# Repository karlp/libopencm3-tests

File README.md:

# Cross target tests for libopencm3

libopencm3(http://github.com/libopencm3/libopencm3) pull requests are often
hard to review.  It can be hard to see the impact on "user" land code, it can
be hard to see how the behaviour changes from a->b.

This repository contains testing frameworks I've put together to help with
cross target testing, with the aim of making them as automated as possible.

General plan is something like....

1. make -C libopencm3 clean all -j8
2. make -C tests/xxx clean all flash test V=1
3. cd libopencm3
4. git checkout proposed-new-code
5. return to step 1

Mileage _will_ vary.

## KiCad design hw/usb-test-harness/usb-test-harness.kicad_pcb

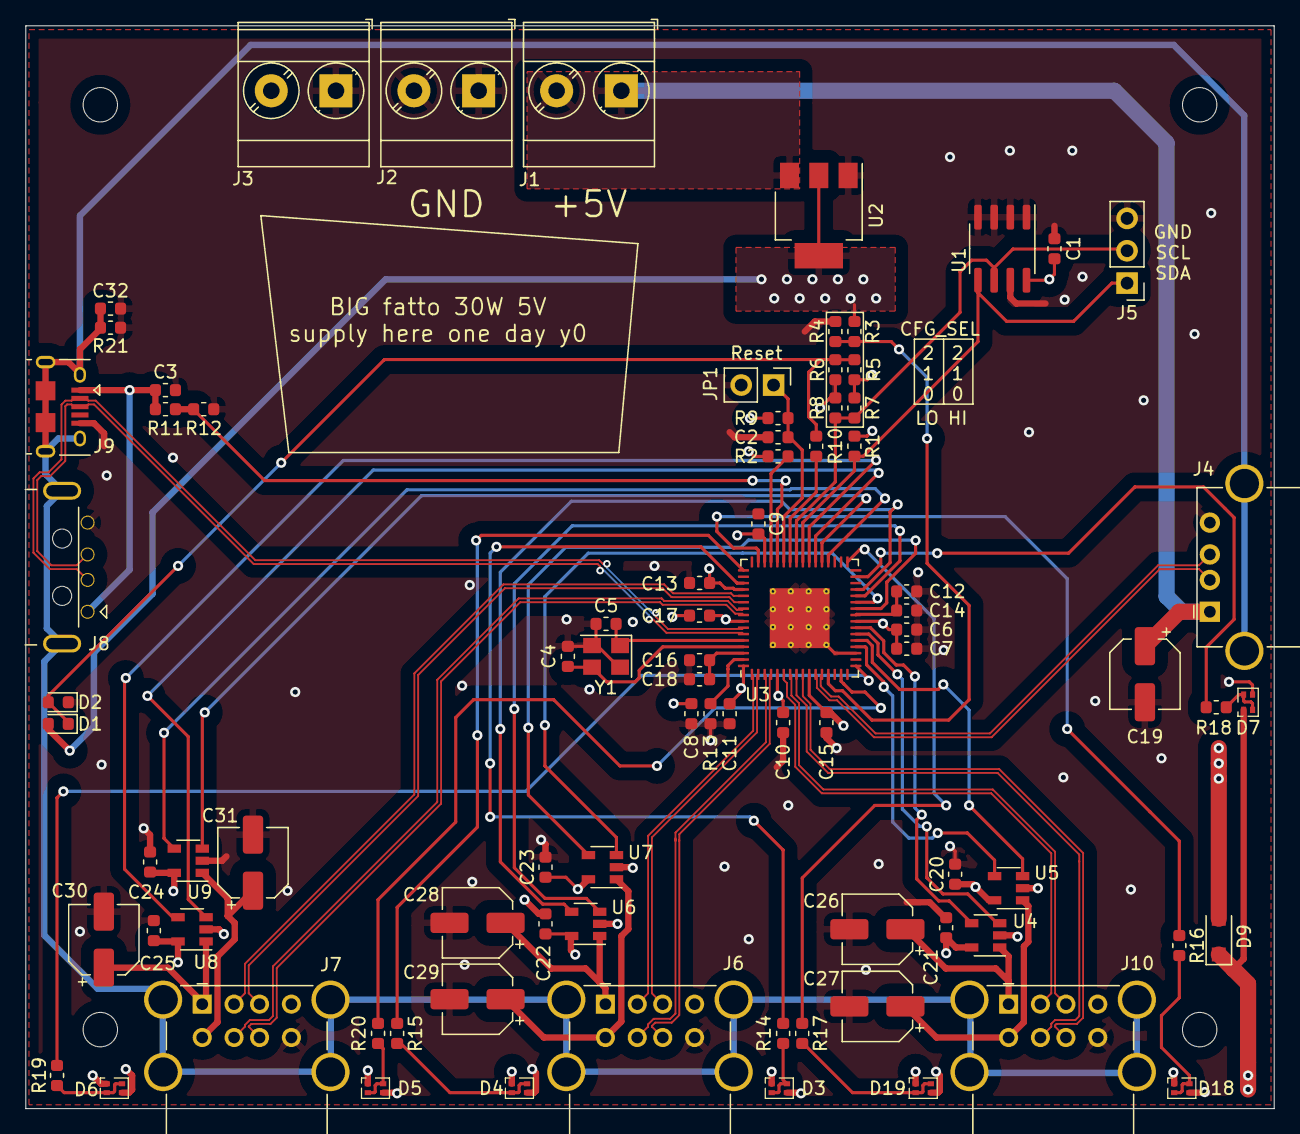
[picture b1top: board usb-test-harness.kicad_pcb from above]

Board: 4 copper layers, 98.0 x 85.0 mm, 88 parts (0 on the bottom side), 67 nets.

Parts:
C1, C2, C7, C9, C10, C11, C13, C14, C15, C17, C18, C32: .1uF; C_0603_1608Metric
C3: 2.2uF; C_0603_1608Metric
C4, C5: 33pF; C_0603_1608Metric
C6, C8, C12, C16, C20, C21, C22, C23, C24, C25: 1uF; C_0603_1608Metric
C19, C26, C27, C28, C29, C30, C31: 100uF; CP_Elec_5x5.4
D1: HS1B; LED_0603_1608Metric
D2: HS1A; LED_0603_1608Metric
D3, D4, D5, D6, D7, D18, D19: LTST-C295KGKRKT; LED_LiteOn_LTST-C295K
D9: D_Small; D_SOD-123F
H1, H2, H3, H4: MountingHole; MountingHole_2.7mm_M2.5
J1: 5V_RAW; TerminalBlock_Phoenix_MKDS-3-2-5.08_1x02_P5.08mm_Horizontal
J2: GND; TerminalBlock_Phoenix_MKDS-3-2-5.08_1x02_P5.08mm_Horizontal
J3: V_EXT; TerminalBlock_Phoenix_MKDS-3-2-5.08_1x02_P5.08mm_Horizontal
J4: USB_A (female down); USB_A_Stewart_SS-52100-001_Horizontal
J5: Conn_01x03_Male; PinHeader_1x03_P2.54mm_Vertical
J6, J7, J10: USB_A_DUAL; USB_A_Wuerth_61400826021_Horizontal_Stacked
J8: USB_A SOFNG USB-05; USB_A_Plug_SOFNG_USB-05
J9: USB_B_Micro (up); USB_Micro-B_Amphenol_10118194-0001LF_Horizontal
JP1: Jumper_NO_Small; PinHeader_1x02_P2.54mm_Vertical
R1, R2, R3, R4, R5, R6, R7, R8: 10k; R_0603_1608Metric
R9, R11, R12: 100k; R_0603_1608Metric
R10, R14, R15, R16, R17, R18, R19, R20, R21: 330; R_0603_1608Metric
R13: 12k; R_0603_1608Metric
U1: FT24C02A; SOIC-8_3.9x4.9mm_P1.27mm
U2: SE5120ST33; SOT-223-3_TabPin2
U3: USB2517; QFN-64-1EP_9x9mm_P0.5mm_EP4.7x4.7mm_ThermalVias
U4, U5, U6, U7, U8, U9: APL3511C; SOT-23-5
Y1: 24MHz; Crystal_SMD_3225-4Pin_3.2x2.5mm

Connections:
+3V3: C1.1, C6.1, C7.1, C8.1, C9.1, C10.1, C11.1, C13.1, C15.1, C17.1, D1.2, D9.2, R1.1, R2.1, R3.1, R5.1, R7.1, R9.1, U1.8, U2.2, U3.5, U3.10, U3.24, U3.46, U3.52, U3.57, U3.64
+5V: C19.1, C20.1, C21.1, C22.1, C23.1, C24.1, C25.1, J1.1, J1.2, J4.1, U2.3, U4.5, U5.5, U6.5, U7.5, U8.5, U9.5
/downstream-port-power/DS+: J4.3, U3.12
/downstream-port-power/DS-: J4.2, U3.11
/downstream-port-power/EN1: U3.23, U4.4
/downstream-port-power/EN2: U3.20, U5.4
/downstream-port-power/EN3: U3.29, U6.4
/downstream-port-power/EN4: U3.26, U7.4
/downstream-port-power/EN5: U3.39, U8.4
/downstream-port-power/EN6: U3.36, U9.4
/downstream-port-power/OC1: U3.22, U4.3
/downstream-port-power/OC2: U3.21, U5.3
/downstream-port-power/OC3: U3.28, U6.3
/downstream-port-power/OC4: U3.27, U7.3
/downstream-port-power/OC5: U3.38, U8.3
/downstream-port-power/OC6: U3.37, U9.3
/downstream-port-power/U1+: J10.3, U3.7
/downstream-port-power/U1-: J10.2, U3.6
/downstream-port-power/U2+: J10.7, U3.9
/downstream-port-power/U2-: J10.6, U3.8
/downstream-port-power/U3+: J6.3, U3.2
/downstream-port-power/U3-: J6.2, U3.1
/downstream-port-power/U4+: J6.7, U3.4
/downstream-port-power/U4-: J6.6, U3.3
/downstream-port-power/U5+: J7.3, U3.54
/downstream-port-power/U5-: J7.2, U3.53
/downstream-port-power/U6+: J7.7, U3.56
/downstream-port-power/U6-: J7.6, U3.55
/downstream-port-power/VBUS1: C26.1, J10.1, U4.1
/downstream-port-power/VBUS2: C27.1, J10.5, U5.1
/downstream-port-power/VBUS3: C28.1, J6.1, U6.1
/downstream-port-power/VBUS4: C29.1, J6.5, U7.1
/downstream-port-power/VBUS5: C30.1, J7.1, U8.1
/downstream-port-power/VBUS6: C31.1, J7.5, U9.1
/upstream-config-leds/CFG_SEL0: J5.2, R7.2, R8.1, U1.6, U3.41
/upstream-config-leds/CFG_SEL1: D1.1, D2.2, R5.2, R6.1, R10.1
/upstream-config-leds/CFG_SEL1_A: R10.2, U3.42
/upstream-config-leds/CFG_SEL2: R3.2, R4.1, U3.13
/upstream-config-leds/EE_SDA: J5.1, R1.2, U1.5, U3.40
/upstream-config-leds/LA_1-3: D3.2, D3.3, R14.2
/upstream-config-leds/LA_2-4: D4.2, D4.3, R15.2
/upstream-config-leds/LA_3-1: D18.2, D18.3, R16.2
/upstream-config-leds/LA_4-2: D19.2, D19.3, R17.2
/upstream-config-leds/LA_5-DS: D7.2, D7.3, R18.2
/upstream-config-leds/LA_6-6: D6.2, D6.3, R19.2
/upstream-config-leds/LA_7-5: D5.2, D5.3, R20.2
/upstream-config-leds/LED_A1: R14.1, U3.51
/upstream-config-leds/LED_A2: R15.1, U3.49
/upstream-config-leds/LED_A3: R16.1, U3.47
/upstream-config-leds/LED_A4: R17.1, U3.33
/upstream-config-leds/LED_A5: R18.1, U3.31
/upstream-config-leds/LED_A6: R19.1, U3.17
/upstream-config-leds/LED_A7: R20.1, U3.15
/upstream-config-leds/LED_DRIVE: D3.1, D4.1, D5.1, D6.1, D7.1, D9.1, D18.1, D19.1
/upstream-config-leds/LOCAL_PWR: R2.2, U3.45
/upstream-config-leds/RBIAS: R13.1, U3.63
/upstream-config-leds/UP+: J8.3, J9.3, U3.59
/upstream-config-leds/UP-: J8.2, J9.2, U3.58
/upstream-config-leds/VBUS_DET: R11.2, R12.1, U3.44
/upstream-config-leds/VBUS_UP: C3.1, J8.1, J9.1, R11.1
/upstream-config-leds/VDD18: C12.1, C14.1, U3.25
/upstream-config-leds/VDD18PLL: C16.1, C18.1, U3.62
/upstream-config-leds/XTAL1: C4.2, U3.61, Y1.3
/upstream-config-leds/XTAL2: C5.2, U3.60, Y1.1
/upstream-config-leds/~RESET: C2.1, JP1.1, R9.2, U3.43
GND: C1.2, C2.2, C3.2, C4.1, C5.1, C6.2, C7.2, C8.2, C9.2, C10.2, C11.2, C12.2, C13.2, C14.2, C15.2, C16.2, C17.2, C18.2, C19.2, C20.2, C21.2, C22.2, C23.2, C24.2, C25.2, C26.2, C27.2, C28.2, C29.2, C30.2, C31.2, C32.1, D2.1, D3.4, D4.4, D5.4, D6.4, D7.4, D18.4, D19.4, J2.1, J2.2, J3.1, J4.4, J5.3, J6.4, J6.8, J7.4, J7.8, J8.4, J9.5, J10.4, J10.8, JP1.2, R4.2, R6.2, R8.2, R12.2, R13.2, R21.1, U1.1, U1.2, U1.3, U1.4, U1.7, U2.1, U3.19, U3.65, U4.2, U5.2, U6.2, U7.2, U8.2, U9.2, Y1.2, Y1.4
GNDPWR: C32.2, J4.5, J6.9, J7.9, J8.5, J9.6, J10.9, R21.2

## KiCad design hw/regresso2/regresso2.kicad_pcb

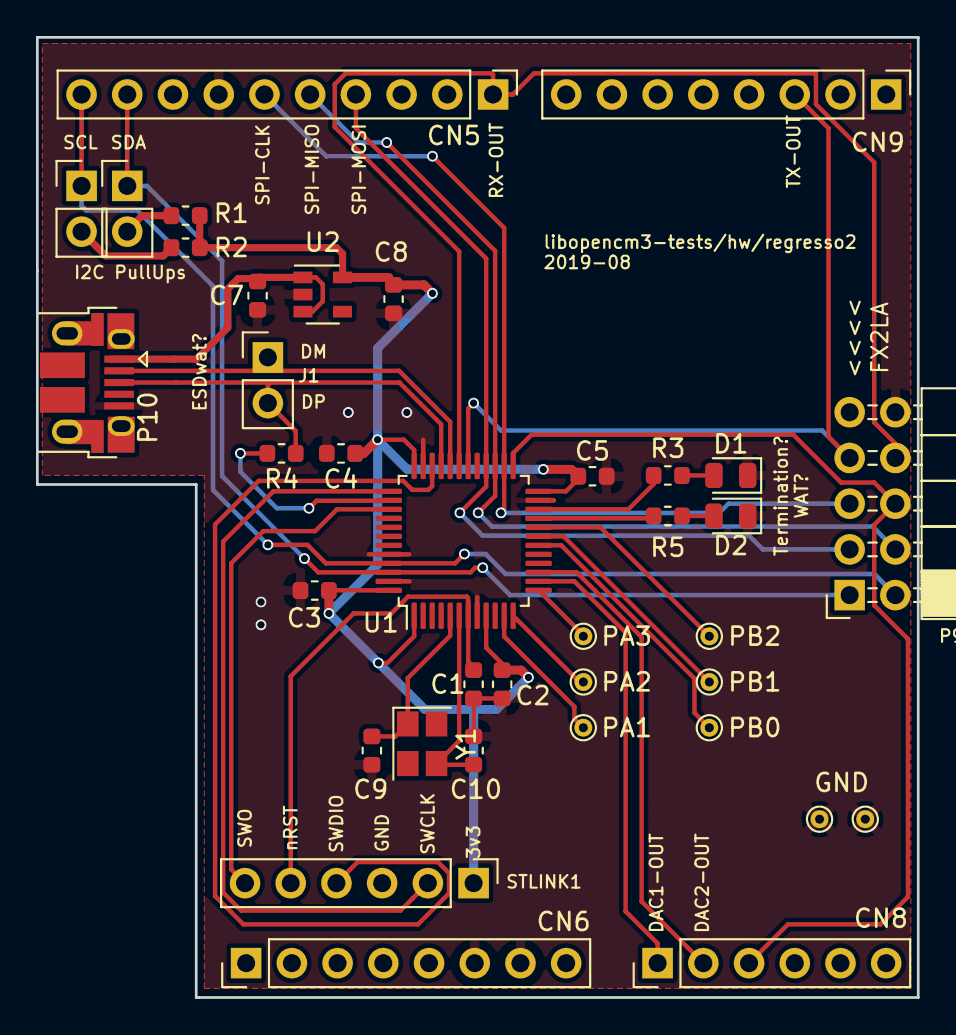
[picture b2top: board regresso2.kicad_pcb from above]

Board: 2 copper layers, 48.9 x 53.3 mm, 37 parts (0 on the bottom side), 34 nets.

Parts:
C1, C2, C3, C4, C5: 100n; C_0603_1608Metric
C7, C8: 1u; C_0603_1608Metric
C9, C10: 12pf; C_0603_1608Metric
CN5: Conn_01x10; PinHeader_1x10_P2.54mm_Vertical
CN6, CN9: Conn_01x08; PinHeader_1x08_P2.54mm_Vertical
CN8: Conn_01x06; PinHeader_1x06_P2.54mm_Vertical
D1: green; LED_0805_2012Metric
D2: red; LED_0805_2012Metric
GND1, GND2: TEST_1P; TestPoint_THTPad_D1.0mm_Drill0.5mm
J1: CONN_01X02; Pin_Header_Straight_1x02_Pitch2.54mm
JP1, JP2: Jumper_NC_Small; Pin_Header_Straight_1x02_Pitch2.54mm
P9: FX2LA; Socket_Strip_Angled_2x05_Pitch2.54mm
P10: CONTROL; USB_Micro-B_Amphenol_10103594-0001LF_Horizontal
PA1, PA2, PA3: TEST_1P; TestPoint_THTPad_D1.0mm_Drill0.5mm
PB0, PB1, PB2: TEST_1P; TestPoint_THTPad_D1.0mm_Drill0.5mm
R1, R2: 4k7; R_0603_1608Metric
R3, R5: 1.5k; R_0603_1608Metric
R4: 1,5k; R_0603_1608Metric
STLINK1: STLINK; Socket_Strip_Straight_1x06_Pitch2.54mm
U1: STM32F303CCTx; LQFP-48_7x7mm_P0.5mm
U2: MIC550x-3.3YM5; SOT-23-5
Y1: Crystal_GND24_Small; Crystal_SMD_SeikoEpson_FA238-4Pin_3.2x2.5mm

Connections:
+3V3: C2.1, C3.1, C4.1, C5.1, C8.1, R1.1, R2.1, STLINK1.1, U1.1, U1.9, U1.24, U1.36, U1.48, U2.5
+5V: C7.1, P10.1, U2.1, U2.3
/DAC1_OUT: CN8.1, U1.14
/DAC2_OUT: CN8.2, U1.15
/I2C_SCL: CN5.10, JP2.1, P9.2, U1.45
/I2C_SDA: CN5.9, JP1.1, P9.1, U1.46
/LED_G: R3.1, U1.22
/LED_R: R5.1, U1.21
/NRST: C1.2, STLINK1.5, U1.7
/SPI_CS: CN8.3, P9.6, U1.25
/SPI_MISO: CN5.5, P9.4, U1.27
/SPI_MOSI: CN5.4, P9.3, U1.28
/SPI_SCK: CN5.6, P9.5, U1.26
/SWCLK: STLINK1.2, U1.37
/SWDIO: STLINK1.4, U1.34
/SWO: STLINK1.6, U1.39
/UART_RX_OUT: CN5.1, P9.8, U1.31
/UART_TX_OUT: CN9.3, P9.7, U1.30
/USB_DM: J1.1, P10.2, U1.32
/USB_DP: J1.2, P10.3, R4.1, U1.33
GND: C1.1, C2.2, C3.2, C4.2, C5.2, C7.2, C8.2, C9.2, C10.2, CN5.7, CN6.6, CN6.7, D1.1, D2.1, GND1.1, GND2.1, P9.10, P10.5, STLINK1.3, U1.8, U1.23, U1.35, U1.44, U1.47, U2.2
unnamed: C9.1, U1.5, Y1.1
unnamed: C10.1, U1.6, Y1.3
unnamed: D1.2, R3.2
unnamed: D2.2, R5.2
unnamed: JP1.2, R1.2
unnamed: JP2.2, R2.2
unnamed: PA1.1, U1.11
unnamed: PA2.1, U1.12
unnamed: PA3.1, U1.13
unnamed: PB0.1, U1.18
unnamed: PB1.1, U1.19
unnamed: PB2.1, U1.20
unnamed: R4.2, U1.38

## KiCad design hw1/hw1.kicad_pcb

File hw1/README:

This is a board designed to receive nucleo64 (and maybe 32) boards
to be test TARGETS.  The stm32l1 on _this_ board is reprogrammed via
one of the debug connectors, with appropriate software to be
master/slave/etc to correspond with the DUT.  All (most) communication
lines between the two boards are tapped to a 10 pin connector matching
cheap FX2based logic analysers, allowing automatic tests to be written
that use sigrok to check that the signals on the wire match expectations.

Notes on assembly hw1-a:
* 16Mhz crystal, 15pf load caps, and 3k7 i2c pullups
  (why don't I have 4k7 0603 resistors lying around? who knows!)
* A power LED wouldn't hurt.
* Adding a red/green user led wouldn't hurt for test pass/fail, even though
  it's meant to be autotest
* maybe a fet to turn on/off the i2c pull ups programatically?
  (maybe just a single jumper? is there really any need for individual control
   of the pullups?)
karlp | http://tinyurl.com/y37mrp5w
23:14:38      englishman | maybe put a second nfet to actually simulate the opendrain i2c peripherals?
23:14:40           Thorn | I reduced the resistors to 2.2K and the drain voltage is now higher
23:15:08           Thorn | should not be a problem with a low Rds(on) mosfet though

* move stlink connector 90° or just down and tuck it in, so we can pull the
  edge in.  It overlaps the buttons on the nucleos, and requires longer
  pins than necessary otherwise.
* Add some ground pads for test points, just in general.  Test points good,
  more test points better.
* capacitor footprints longer than needed, were these the "hand solder" variants?

Notes on schematic "lessons"

* i2c on pb8/9 aren't actually on CN5, A4/A5 by default, only if you change solder bridges.
  => need to move the i2c pullups and inputs to the host hw1 board over to their default location
  on CN5 D14/D15!
* uart on pa2/3 on cn9 aren't by default, they're routed to the onboard stlinks of nucleos.
  Is there a uart on any pins available by default?!!
  PB6 is available for uart-tx, (usart1) CN5 pin3 (already in use for spi!)
  PA9 is _also_ usart-tx (usart1) CN5-pin1
  pa10 is available! usart1-rx CN9-pin3
* SPI CS, on PB6, despite the nucleo user manual saying is available.  isn't.  It's not in
  the AF table, or the pin descriptions for PB6.
  => Need to find another spi cs if you want to test hardware css control
	nucleo docs only mention spi1, which from above is busted.  Is there another?
  PA4! on CN8 SPI1 NSS, same SPI1 as we're using already
  I had discounted this originally, as it was the only pin the dac is available on, for the parts with only a single dac channel
  (This is DAC from the _DUT_ so can't be moved)
* pin numbers on arduino hheaders doesn't match numbering in the nucleo user manuals, which just makes things hard.

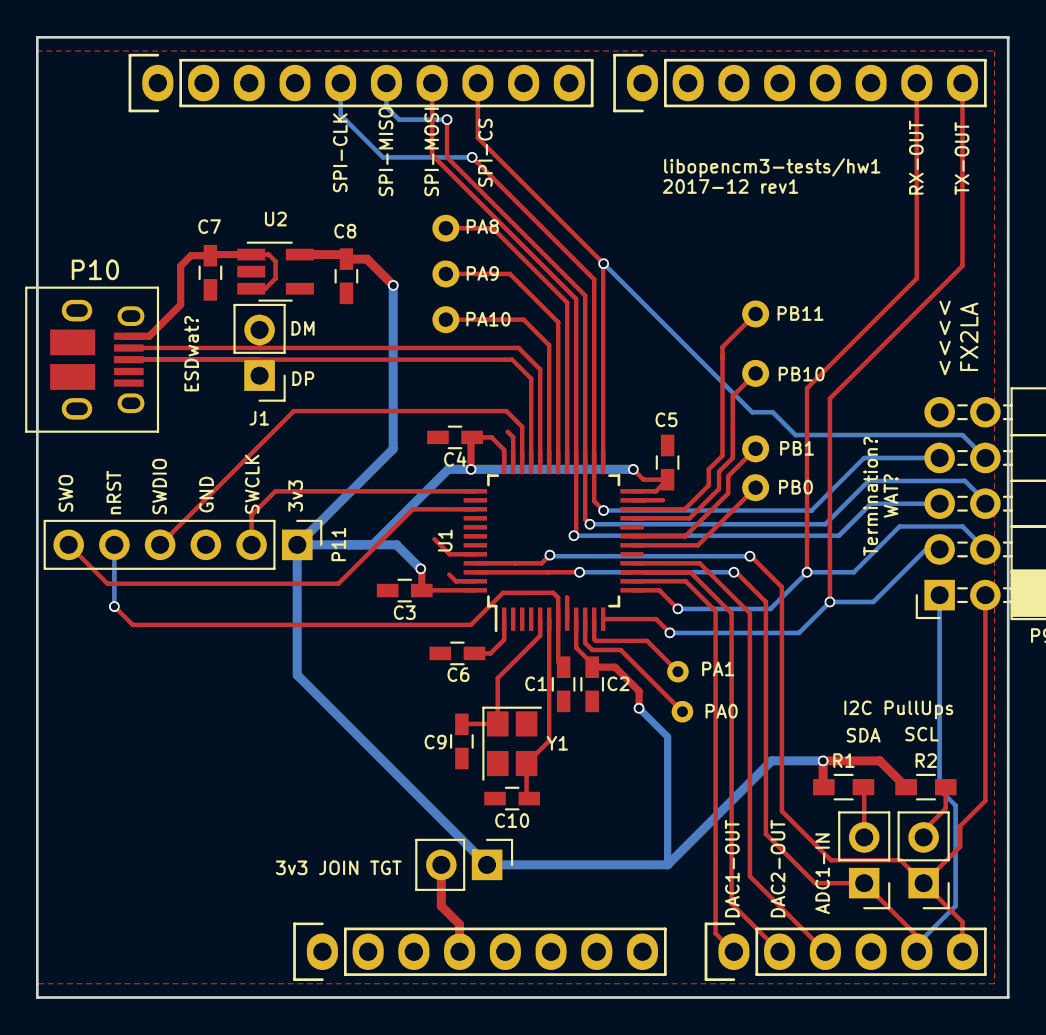
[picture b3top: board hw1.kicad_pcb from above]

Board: 2 copper layers, 53.9 x 53.3 mm, 35 parts (0 on the bottom side), 35 nets.

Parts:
C1, C2, C3, C4, C5, C6: 100n; C_0603_HandSoldering
C7, C8: 1u; C_0603_HandSoldering
C9, C10: 18pf; C_0603_HandSoldering
J1: CONN_01X02; Pin_Header_Straight_1x02_Pitch2.54mm
JP1, JP2, JP3: Jumper_NC_Small; Pin_Header_Straight_1x02_Pitch2.54mm
P1: Power; Socket_Strip_Arduino_1x08
P2: Analog; Socket_Strip_Arduino_1x06
P3: Digital; Socket_Strip_Arduino_1x10
P4: Digital; Socket_Strip_Arduino_1x08
P9: FX2LA; Socket_Strip_Angled_2x05_Pitch2.54mm
P10: CONTROL; USB_Micro-B_10103594-0001LF
P11: CONN_01X06; Socket_Strip_Straight_1x06_Pitch2.54mm
PA0, PA1, PA8, PA9, PA10: TEST_1P; Measurement_Point_Round-TH_Small
PB0, PB1, PB10, PB11: TEST_1P; Measurement_Point_Round-TH_Small
R1, R2: 4k7; R_0603_HandSoldering
U1: STM32L151C6TxA; TQFP-48_7x7mm_Pitch0.5mm
U2: MIC550x-3.3YM5; SOT-23-5_HandSoldering
Y1: Crystal_GND24_Small; Crystal_SMD_SeikoEpson_FA238-4pin_3.2x2.5mm

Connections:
+3V3: C2.1, C3.1, C4.1, C5.1, C8.1, JP3.1, P11.1, R1.1, R2.1, U1.9, U1.24, U1.36, U1.48, U2.5
+5V: C7.1, P10.1, U2.1, U2.3
/ADC_IN1: P2.3, U1.16
/DAC1_OUT: P2.1, U1.14
/DAC2_OUT: P2.2, U1.15
/I2C_SCL: JP2.1, P2.6, P9.2, U1.45
/I2C_SDA: JP1.1, P2.5, P9.1, U1.46
/NRST: C1.2, P11.5, U1.7
/SPI_CS: P3.8, P9.8, U1.25
/SPI_MISO: P3.6, P9.6, U1.27
/SPI_MOSI: P3.7, P9.5, U1.28
/SPI_SCK: P3.5, P9.7, U1.26
/SWCLK: P11.2, U1.37
/SWDIO: P11.4, U1.34
/SWO: P11.6, U1.39
/UART_RX_OUT: P4.7, P9.4, U1.13
/UART_TX_OUT: P4.8, P9.3, U1.12
/USB_DM: J1.2, P10.2, U1.32
/USB_DP: J1.1, P10.3, U1.33
/VLCD: C6.2, U1.1
GND: C1.1, C2.2, C3.2, C4.2, C5.2, C6.1, C7.2, C8.2, C9.2, C10.2, P1.6, P1.7, P3.4, P9.10, P10.5, P11.3, U1.8, U1.23, U1.35, U1.44, U1.47, U2.2
unnamed: C9.1, U1.5, Y1.1
unnamed: C10.1, U1.6, Y1.3
unnamed: JP1.2, R1.2
unnamed: JP2.2, R2.2
unnamed: JP3.2, P1.4
unnamed: PA0.1, U1.10
unnamed: PA1.1, U1.11
unnamed: PA8.1, U1.29
unnamed: PA9.1, U1.30
unnamed: PA10.1, U1.31
unnamed: PB0.1, U1.18
unnamed: PB1.1, U1.19
unnamed: PB10.1, U1.21
unnamed: PB11.1, U1.22

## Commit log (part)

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2015-10-16 purpose of shared directory
2015-10-16 purpose of first test
2015-10-16 initial openocd config files
2015-10-17 fix markdown
2015-10-17 WIP: adc-power f3
    needs rcc fixups
2015-10-28 f3: wip continues
2015-11-03 f4: proper float/int temp readings
2015-11-03 WIP: f0 adc build
2016-03-04 f0 working (one fixme)
    need scan mode upstream?
2016-03-04 attempt actual adc on l4
    (insufficient,needs clocks yet)
2016-03-04 f3: use new rcc names
2016-03-14 fix l4 to run at 48Mhz and with a clock
2016-03-30 adc: f4: update for new naming
2016-03-30 rules: attempt to connect to a running openocd first.
2016-03-30 adc: hacks to get it up and running for L4
2016-08-18 rcc-legal-ranges: initial l1 setup
    Doesn't fail on my l1 disco unfortunately. (silicon rev X)
    Does fail on a custom board with silicon rev V
2016-08-19 rcc-legal-ranges: run through a range of clocks
    blink fast/slow for each clock configuration tested, then finish by
    blinking idly.
    As of this commit, this test fails quickly on most L1 boards tested.
    An update to libopencm3 is required to fix this.
2016-09-09 adc-power: add oocd file for f3 disco
2016-09-09 switch to using devices.data linker generation
    Still using my own private rules, but now using the linker script generator so
    no need to keep expanding on including .ld files in core libopencm3
2016-09-09 squelch errors from netcat when it needs to start oocd
    be nice if I could _keep_ errors when V=1 but....
2016-09-09 adc-power: f3 adc peripheral takes over gpios automatically?
    Doesn't seem to have any impact when just hooking up a pot to the pins
    at least.
2016-09-09 update libopencm3 to get adc power off fixes
2016-09-26 update library
2016-09-26 ubs-serial-rs485: First solidly working version.
    Needs major refactoring to split out the _actual_ arch dependent pieces.
    Needs parity and more complete baud rate support.
    Needs rs485 support.
2016-09-30 usb-serial: functional on f1.
2016-09-30 rules.mk: don't bother making .bins
2016-09-30 usb-rs485: update readme
2016-10-03 oocd: use l0 for f1 instead.
    let's me have both f1 and f4 in operation at the same time
2017-02-21 usb-rs485: update to latest library master
2017-02-21 i2c: Initial stub import of old f4 code
    Currently (despite docs) is an import of code reading the onboard i2c
    peripheral
2017-02-21 i2c-master: start extracting out i2c code
    Working on f4 with an external sht21 i2c sensor.
    Still lots of f4 specifics yet. But, progress.
2017-03-08 i2c-master: working on l1 too.
    Needs retest on f4. then ready to move to new hardware
2017-03-08 lib: Bump to my current staging tree
2017-03-09 i2c: draft api of "set speed 100k" common
    Only needs the input clock in megahz.
2017-03-22 use transfer style for serial number reading
2017-03-22 working temp/humi stop/repeated stuff on f0
    needs cleanup and remerge with f4/l1
2017-03-23 i2c-master: cleaned up again on l1
    now has repeated-start and stop/start support, with the same API as v2
    Just to decide whether all of it goes up into the library or not.
2017-03-23 i2c: use speed setting from newer library version
2017-03-27 i2c-master: add pins for f0 disco
2017-03-27 update to latest staging
2017-04-04 rules.mk: make sure flashing works from other directories
    Provide full path when communicating with openocd.
    This means you can run a permanent openocd session from the ./openocd
    directory, and still have things working with just "make flash" from
    whatever test directory you are in.
2017-04-04 move forward to new libopencm3
2017-04-05 i2c: fix uart notes for f0
2017-09-01 awd-timer-dma: initial commit.
    Had to figure out a few screwups before I got the AWD working properly.
2017-10-07 WIP: hardware test partner round 1
    Not sure which kicad files are necessary and which are local yet!
    Goal: fixed "host" board (this board) with socket for _any_ Nucleo64 st
    board, giving access to test:
    * DAC->ADC (both directions)
    * I2C (both directions)
    * SPI (both directions)
2017-10-24 uart-basic: add f0, requires newest code too
    stupid f072 disco doesn't have usart2 available
2017-10-25 uart-basic: add l4
2017-10-26 common openocd: use -s to find files from test dirs.
    The sourcing of the common.cfg and the optional local files was failing
    when invoked from a test directory. Use -s and properly use [find ...]
    to search paths nicely.
2017-11-17 gitignore kicad .bak files
2017-11-17 git ignore more backups
2017-11-17 hw1: apparently _actually_ save the file
2017-11-20 hw1: add crystal, more commentary
    probably need a crystal for usb :)
    still needs footrints, will probably be any old 3225 part.
2017-12-11 hw1: continued, just intermediate progress save
    wtf kicad, why aren't my grounds connected?!
2017-12-17 new pdf for current schematic
2017-12-27 hw1: drop arduinno style holes and board shape
    More to go, nno need for the silk and dead shapes, we just needed the
    pin spacings
2017-12-28 hw1: cleanup silk and start adding labels
2017-12-29 hw1: discover reversed numbering on arduino connectors
    joy. Fixed now against nucleo64 manuals.
2017-12-29 hw1: commit with filled pours
2018-02-02 hw1: add exampe part number for fx2la part number
2018-02-19 hw1: notes on signal integrity
2018-02-19 spi-master: update to run on the hw1 host board
    "TRIGGER" is now D0 on the fx2 port
    "LED" is now D1 on the fx2 port,
    "SPI MOSI" is now D4 on the fx2
    "SPI MISO" is now D5
    "SPI CLOCK" is now D6
2018-02-21 adc-power: stm32l1: make "generic" == hw1 test board.
    * use the trigger pin instead of the led.
    * use the smaller flash of the part mounted.
2018-02-22 uart-basic: initial hacks for dut board.
    but oh joy, solder bridges are wrong for serial to hw1 host by defualt
    :(
2018-02-25 adc-power: drop unused l053 makefile stub
    remnant of being copied from usb-gadget0
2018-02-25 i2c-master: add parallel make and fix errors
    Fix bugs from outof date libopencm3
2018-04-16 spi-master-l0: wip:
    doesn't work, but getting there
2018-08-27 update to current libopencm3 master
2018-09-02 freertos-gadget-zero: basic test it all works.
    No other tasks, but makes sure it runs and passes the tests
2018-09-10 rules: support .S assembly files too.
    We just list them in "CFILES" which is a little wrong, but super simple
2018-09-10 host-spi-slave side ported to rtos2
2018-09-10 rtos2-usb-spi-mster: compiles but broken.
    Need to save my work for a bit
2018-09-11 ignore more bin directories
2018-09-14 rtos2-spi-host: properly wait for events.
    THis fixes USB task running as a higher priority task, but only when it
    needs to. The ISR sets a flag, and the task runs and turns the irq back
    on. This now properly shares priorities by yielding when it's waiting
    for events.
2018-09-19 rules.mk: turn unused variable warnings back on
2018-09-19 update libopencm3
2018-09-19 BORKNE: trying to get gadget0 properly using events in rtos
2018-09-19 STILL BORKED: rtx enumerates but won't pass tests.
    normally works, but too many pipe errors. just not reliable.
    No idea why. is it a queue of irq events it's not handling?
2019-01-13 freertos-spi-slave: usb controlled spi transfers
    Not optimal, and not tested with a functional spi slave for the inbound
    path, but functional valid usb controlled spi transfers in the out
    direction.
    Tested different bauds. cpha/cpol.... makes changes, but not sure it's
    entirely correct? Might be a sigrok problem?
    Contains a "test" python script that makes a pair of transfers on each
2019-01-15 extract freertos makefile snippet
2019-01-15 spi slave: update pinout docs
2019-01-16 non-functional spi slave for L0
    Overrun errors. Shelving and moving it to an m3 project with trace
    debug
2019-01-16 spi-slave: semi sort of spi slave on l1
    Can't get the rx "command" bytes into the task state before it's already
    tried to reply. queue reads and writes trace out to the "right"
    commands, but not in time
2019-05-13 works? but nothing that should have maattered? holding it as a commit anyway
2019-05-27 spi dut: use pullups to try and hold state better
    Seems to eliminate a lot of noise when things were disabled at each end
    when using pulseview at least.
    No guarantees that this fixes things really.
2019-05-27 spi slave host: use a separate oocd file
    needs different ports and a different name to be sure I'm on the host.
    host is always the l1 on the "hw1" board for now.
2019-05-27 spi slave host: hack: add usb control req to control CS pin directly
    Should at least get a define.
2019-05-27 spi slave host: more testing for reg style
    still doesnt work more than once though.
2019-08-15 openocd: add more serials
2019-08-15 spi-slave: dut: more adventures with the dumb version
    still doesn't work, but making progress
2019-08-15 spi slave: dut: stash another not quite working version
    keep seeing 0x81 instead of 0x2 or 0x3 for the read register.
    something's fishy, even across all the versions now.
2019-08-15 spi slave dut: more pointless hacking with no result.
    stash work before burning it all
2019-08-15 spi-slave: comment out some tests while getting basics working
2019-08-19 hw/regresso2: improvements to the test platform, a abit at least
    starting out with notes from last time.
2019-08-26 adc-power: update apis
2019-08-28 regresso2: board fixed
2019-08-28 regresso2: straighten line on board outline
2019-12-03 insane ideas on our own usb hub board
    stackable sideways to make it easier to lay out
    chainable power terminals
    dual "DUT" usb ports for discovery/etc boards with an stlink and a user
    usb port.
2019-12-03 hw: usb test harness: add docs
2020-01-10 usb-test-harness: save point before refactor
    We moved to usb2517 to keep config simple, but we're about to gut the
    symbol and break the schematic apart even further.
2020-01-11 hw: usb-test-harness: split, heirarchical
2020-02-28 usb-test-harness: updated usb footprints, working on it again
    Just trying to finalise the connectors before getting down to brass
    tacks
2020-03-08 hub: we've chosen leds poorly.
    We can't _really_ get away with using two discrete leds to try and get a
    bicolour effect, it's just going to be weird.
    A side mount bi colour independent woudl be good, but cant' find one
    cheaply, and top mount will be fine I think....
2020-03-10 usb-hub: pickd SOD-123F as footprint for diodes
    SMA is very common, but bigger, SOD-123F is just as cheap, and more than
    suitable.
2020-03-11 usb-hub: switch to newer amphenol micro b
    this makes it feasible to route usb properly. Then, charge ahead with
    routing. Started with the 3v3 and hub power parts, now continuing with
    the enable/overcurrent parts. leds will be last.
2020-03-11 usb-hub: finish all enable/oc lines, fix warnings
    just leds, led drive, usb shields, and the big 5v mainline left.
2020-03-11 usb-hub: fix more diff pairs broken by moving things.
2020-03-13 usb-hub: add local power connection
    Somehow felt that "dynamic power" was going to magically save things
    here. It does not! required a bit of re-routing.
2020-03-14 usb-hub: decide shields per app note
    SMSC 15.17 guidelines for usb hubs seem sensible and relevant.
    Connect all the shields together, and to ground at one point.
2020-03-20 usb-hub: sch notes on todo, esd protection and inrush
    pcb only had silk pushing i think. kicad nightlies are trashing diffs
    :|
2020-10-16 usb-test-harness moved to github.com/karlp/hubbish
    Moved out as it's own project
2020-10-16 i2c-master: f4: update clock apis to current
2020-10-16 i2c-master: fix sht21 serial readout
    This more closely matches original sensiron docs
2023-01-19 drop all dangling funcgen stuff
2023-01-20 functional spi master... but no DFU?!
2023-02-28 dfu-spi: deadend: you should add dfu to the existing spi tests!
2023-02-28 tests: freertos-spi-slave: update to 2023
    newest stable freertos, clarify readme
2023-03-01 UNTESTED: freertos-spi-slave: host: add DFU support
    compiles, but needs testing
2023-03-06 freertos-spi-slave/host: deglitch CS
